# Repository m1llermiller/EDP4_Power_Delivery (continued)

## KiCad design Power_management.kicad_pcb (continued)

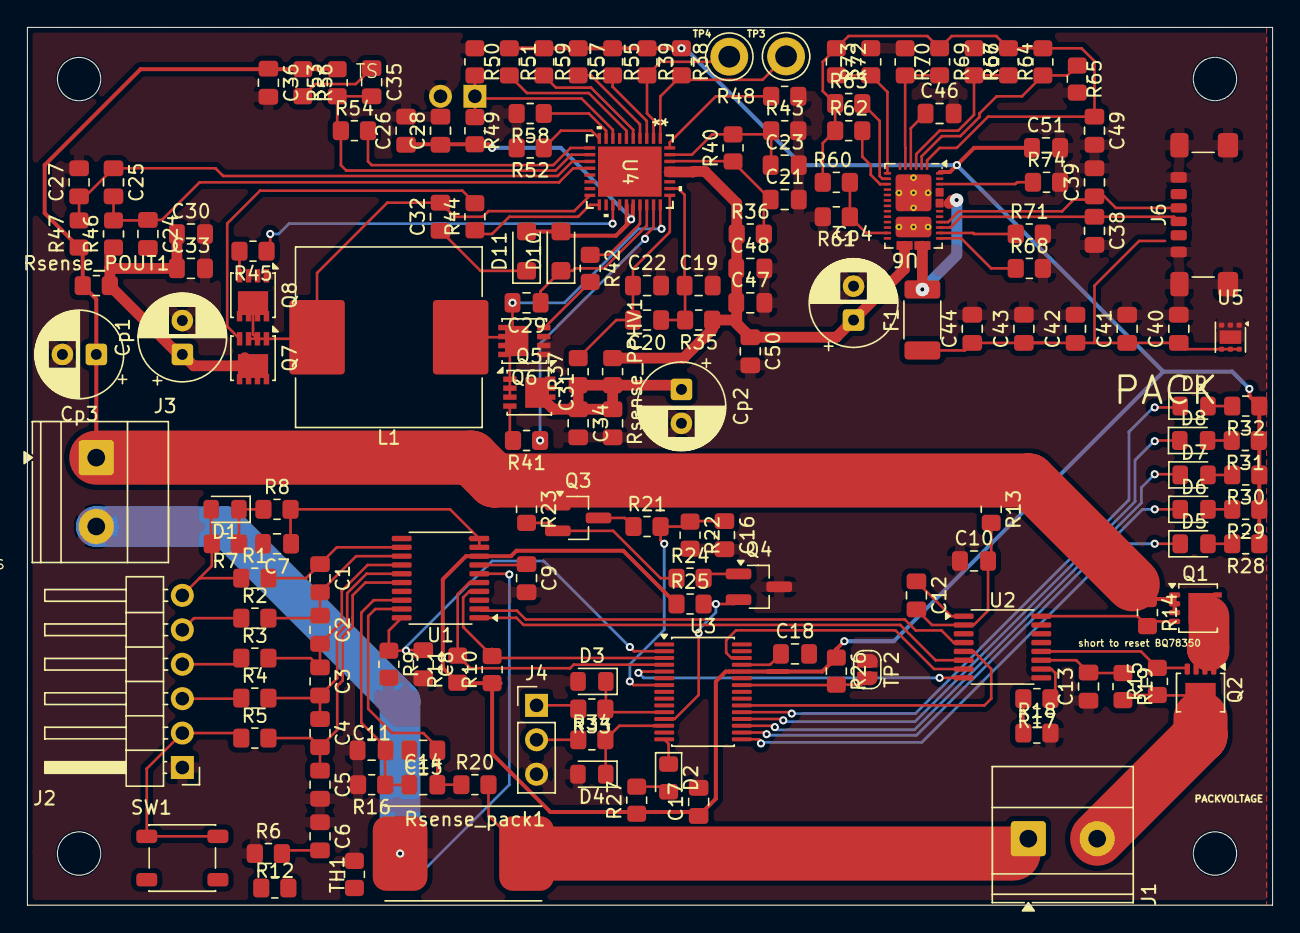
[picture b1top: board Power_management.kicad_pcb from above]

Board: 2 copper layers, 91.9 x 64.8 mm, 172 parts (1 on the bottom side), 113 nets.

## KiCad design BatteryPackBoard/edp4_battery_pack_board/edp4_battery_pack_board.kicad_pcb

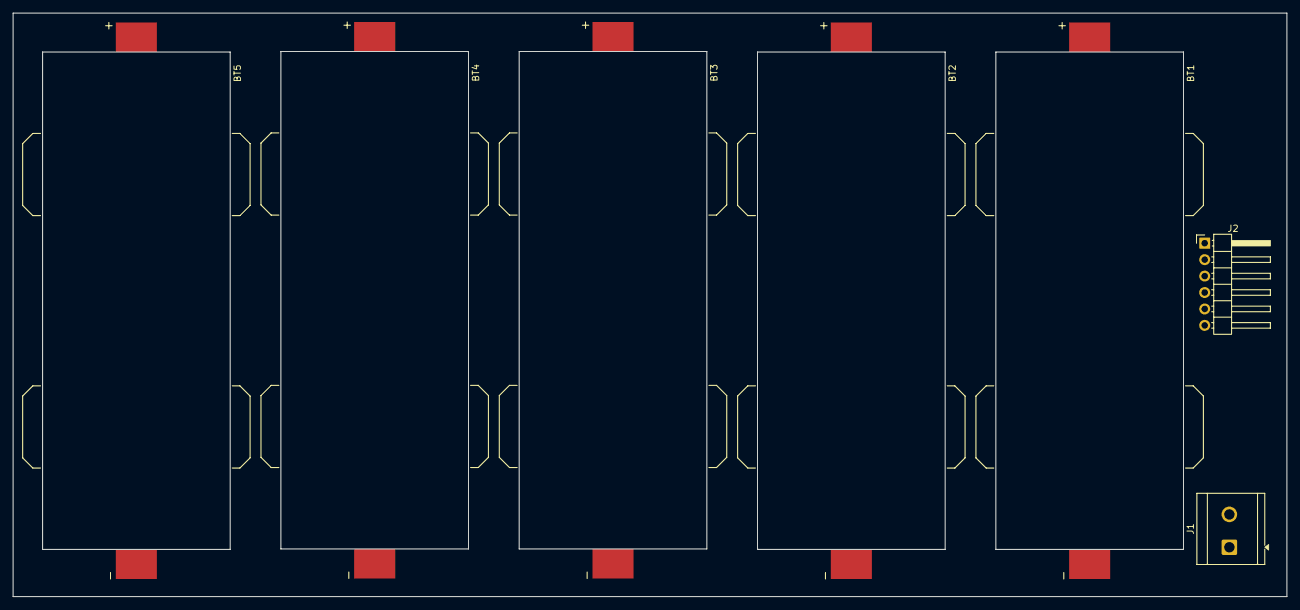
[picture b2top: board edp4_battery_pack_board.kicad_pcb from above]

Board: 2 copper layers, 196.8 x 90.2 mm, 7 parts (0 on the bottom side), 2 nets, no tracks yet.

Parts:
BT1, BT2, BT3, BT4, BT5: Battery_Cell; BAT_1106
J1: Conn_01x02_Socket; TerminalBlock_CUI_TB007-508-02_1x02_P5.08mm_Horizontal
J2: Conn_01x06; PinHeader_1x06_P2.54mm_Horizontal

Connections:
unnamed: J1.1, J2.1
unnamed: J1.2, J2.6

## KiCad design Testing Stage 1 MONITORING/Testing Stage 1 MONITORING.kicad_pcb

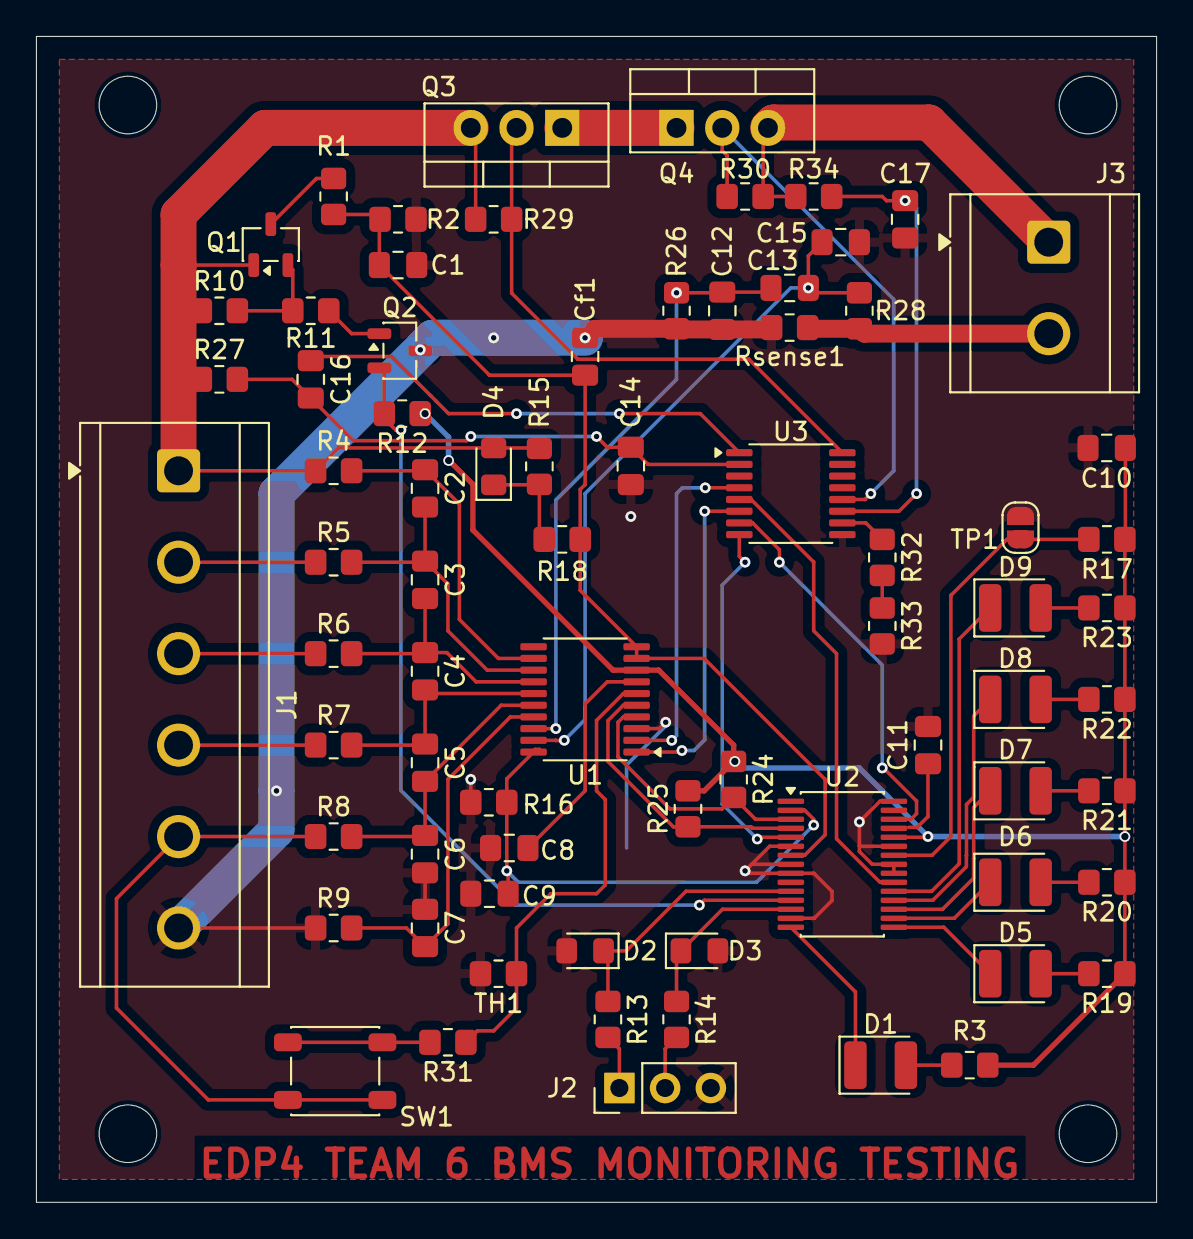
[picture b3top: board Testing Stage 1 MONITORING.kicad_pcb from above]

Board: 2 copper layers, 62.2 x 64.8 mm, 79 parts (0 on the bottom side), 60 nets.

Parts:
C1: 3300pF; C_0805_2012Metric_Pad1.18x1.45mm_HandSolder
C2, C3, C4, C5, C6, C7: 1u; C_0805_2012Metric_Pad1.18x1.45mm_HandSolder
C8, C10, C11, C12, C13, C15: 0.1u; C_0805_2012Metric_Pad1.18x1.45mm_HandSolder
C9: 470p; C_0805_2012Metric_Pad1.18x1.45mm_HandSolder
C14, C16: 470n; C_0805_2012Metric_Pad1.18x1.45mm_HandSolder
C17: 10n; C_0805_2012Metric_Pad1.18x1.45mm_HandSolder
Cf1: 2.2u; C_0805_2012Metric_Pad1.18x1.45mm_HandSolder
D1, D5: 599-2100-137F; LED_1210_3225Metric
D2, D3: 5.6V; D_0805_2012Metric_Pad1.15x1.40mm_HandSolder
D4: 100V; D_0805_2012Metric_Pad1.15x1.40mm_HandSolder
D6, D7, D8, D9: LED; LED_1210_3225Metric
H1, H2, H3, H4: MountingHole; MountingHole_3.2mm_M3
J1: Conn_01x06_Socket; TerminalBlock_CUI_TB007-508-06_1x06_P5.08mm_Horizontal
J2: Conn_01x03_Pin; PinHeader_1x03_P2.54mm_Vertical
J3: Conn_01x02; TerminalBlock_CUI_TB007-508-02_1x02_P5.08mm_Horizontal
Q1: PMOS; SOT-23-3
Q2: NMOS; SOT-23-3
Q3, Q4: NMOS; TO-220-3_Vertical
R1, R32: 300k; R_0805_2012Metric_Pad1.20x1.40mm_HandSolder
R2, R33: 16k; R_0805_2012Metric_Pad1.20x1.40mm_HandSolder
R3, R19, R20, R21, R22, R23: 10; R_0805_2012Metric_Pad1.20x1.40mm_HandSolder
R4, R5, R6, R7, R8, R9: 1k; R_0805_2012Metric_Pad1.20x1.40mm_HandSolder
R10, R11, R17: 100k; R_0805_2012Metric_Pad1.20x1.40mm_HandSolder
R12: 1M; R_0805_2012Metric_Pad1.20x1.40mm_HandSolder
R13, R14, R18, R26, R27, R28, R34: 100; R_0805_2012Metric_Pad1.20x1.40mm_HandSolder
R15, R24, R25, R31: 10k; R_0805_2012Metric_Pad1.20x1.40mm_HandSolder
R16: 500k; R_0805_2012Metric_Pad1.20x1.40mm_HandSolder
R29, R30: 10M; R_0805_2012Metric_Pad1.20x1.40mm_HandSolder
Rsense1: 15m; R_0805_2012Metric_Pad1.20x1.40mm_HandSolder
SW1: SW_Push; SW_SPST_PTS647_Sx38
TH1: 10k; R_0805_2012Metric_Pad1.20x1.40mm_HandSolder
TP1: TestPoint_2Pole; SolderJumper-2_P1.3mm_Open_RoundedPad1.0x1.5mm
U1: BQ76920PW; TSSOP-20_4.4x6.5mm_P0.65mm
U2: BQ78350DBT; TSSOP-30_4.4x7.8mm_P0.5mm
U3: BQ76200PW; TSSOP-16_4.4x5mm_P0.65mm

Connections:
/ALERT_AFE: C9.1, R16.1, U1.20 (ALERT), U2.2 (ALERT)
/BAT: C1.1, Cf1.1, R1.2, R2.1, R18.2, U1.9 (REGSRC), U1.10 (BAT), U2.7 (BAT)
/CHG: U1.2 (CHG), U3.4 (CHG_EN)
/CHG_GATE: Q3.2 (G), R29.2, U3.16 (CHG)
/Cell_one: J1.5, R8.1, SW1.2
/DSG: U1.1 (DSG), U3.6 (DSG_EN)
/DSG_GATE: Q4.2 (G), R30.2, U3.12 (DSG)
/HS_SW_CP_EN: U2.21 (GPIO_A), U3.5 (CP_EN)
/HS_SW_PCHG_EN: U2.5 (~PRECHG), U3.8 (PCHG_EN)
/HS_SW_PMON_EN: U2.28 (GPIO_B), U3.7 (PMON_EN)
/LED1: D5.1 (K), U2.16 (LED1)
/LED2: D6.1 (K), U2.17 (LED2)
/LED3: D7.1 (K), U2.18 (LED3)
/LED4: D8.1 (K), U2.19 (LED4)
/LED5: D9.1 (K), U2.20 (LED5)
/PACK+: J3.1, Q4.3 (S), R30.1, R34.2
/PACK-: J3.2, R28.2, Rsense1.2
/PWRM: D1.1 (K), U2.15 (PWRM)
/SCL_AFE: R25.2, U1.5 (SCL), U2.4 (SCL)
/SDA_AFE: R24.2, U1.4 (SDA), U2.3 (SDA)
/SMBC: D3.1 (K), R14.1, U2.13 (SMBC)
/SMBD: D2.1 (K), R13.1, U2.11 (SMBD)
/SRN: C13.2, C15.1, R28.1, U1.19 (SRN)
/SRP: C12.1, C13.1, R26.1, U1.18 (SRP)
/TS1_AFE: R31.1, TH1.1, U1.6 (TS1)
/Top_cell_stack: D4.2 (A), J1.1, Q1.1 (D), Q3.3 (S), R4.1, R10.1, R15.1, R27.1, R29.1
/VCC: C10.1, R3.1, R12.1, R17.1, R19.1, R20.1, R21.1, R22.1, R23.1, R24.1, R25.1, U1.8 (REGOUT), U2.26 (VCC)
/VEN: Q2.2 (G), R12.2, U2.12 (VEN)
GND: C1.2, C6.2, C7.1, C8.2, C9.2, C10.2, C11.2, C12.2, C14.1, C15.2, C17.1, Cf1.2, D2.2 (A), D3.2 (A), J1.6, J2.3, Q2.3 (S), R2.2, R9.1, R16.2, R26.2, R33.2, Rsense1.1, TH1.2, TP1.1, U1.3 (VSS), U2.6 (VAUX), U2.8 (~PRES), U2.9 (~KEYIN), U2.14 (~DISP), U2.22 (VSS), U2.23 (VSS), U2.25 (VSS), U2.30 (SMBA), U3.9 (VSS)
unnamed: D1.2 (A), R3.2
unnamed: D4.1 (K), R15.2, R18.1
unnamed: D5.2 (A), R19.2
unnamed: D6.2 (A), R20.2
unnamed: D7.2 (A), R21.2
unnamed: D8.2 (A), R22.2
unnamed: D9.2 (A), R23.2
unnamed: J1.2, R5.1
unnamed: J1.3, R6.1
unnamed: J1.4, R7.1
unnamed: J2.1, R13.2
unnamed: J2.2, R14.2
unnamed: Q1.2 (G), R10.2, R11.1
unnamed: Q1.3 (S), R1.1
unnamed: Q2.1 (D), R11.2
unnamed: Q3.1 (D), Q4.1 (D)
unnamed: R31.2, SW1.1
unnamed: R32.2, R33.1
unnamed: C8.1, U1.7 (CAP1)
unnamed: C7.2, R9.2, U1.17 (VC0)
unnamed: C5.2, C6.1, R8.2, U1.16 (VC1)
unnamed: C4.2, C5.1, R7.2, U1.15 (VC2)
unnamed: C3.2, C4.1, R6.2, U1.14 (VC3)
unnamed: C2.2, C3.1, R5.2, U1.13 (VC4)
unnamed: C2.1, R4.2, U1.12 (VC5)
unnamed: C11.1, U2.27 (RBI)
unnamed: R17.2, TP1.2, U2.24 (~MRST)
unnamed: C14.2, C16.2, R27.2, U3.2 (BAT)
unnamed: C17.2, R34.1, U3.11 (PACK)
unnamed: R32.1, U3.10 (PACKDIV)
unnamed: C16.1, U3.1 (VDDCP)

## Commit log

2026-01-30 setup
2026-01-30 beginning fuel gage layout
2026-01-30 gitignore
2026-01-30 starting usb pd charging
2026-02-08 usb pd charging
2026-02-26 progress
2026-03-03 progress on cell fuel gage
2026-03-06 structural changes
2026-03-07 development stage 1 - testing board for AFE / Fuel gage / high side protection controller - unfinished
2026-03-09 need to fix high side control IC - no need for precharge system
2026-03-10 fixed schematic, changed high side FETs, rough layout, still need to change footprints to 0805 so can be manufactured cheap at uni
2026-03-10 routing and layout updates
2026-03-10 updated layout and almost complete routing - need to address DRC
2026-03-10 working layout and routing no DRC error - but ugly
2026-03-16 refinements - moving battery pack off the PCB
2026-03-20 adding charging stages finally
2026-03-20 finished charger schematic - still need to finalise usb
2026-04-01 working on the routing
2026-04-02 routing updates
2026-04-08 compact routing- will address DRC errors
